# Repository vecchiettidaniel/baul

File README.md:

# caja-negra
Aca va todo lo que quiero tener dispnible, es un pendrive online

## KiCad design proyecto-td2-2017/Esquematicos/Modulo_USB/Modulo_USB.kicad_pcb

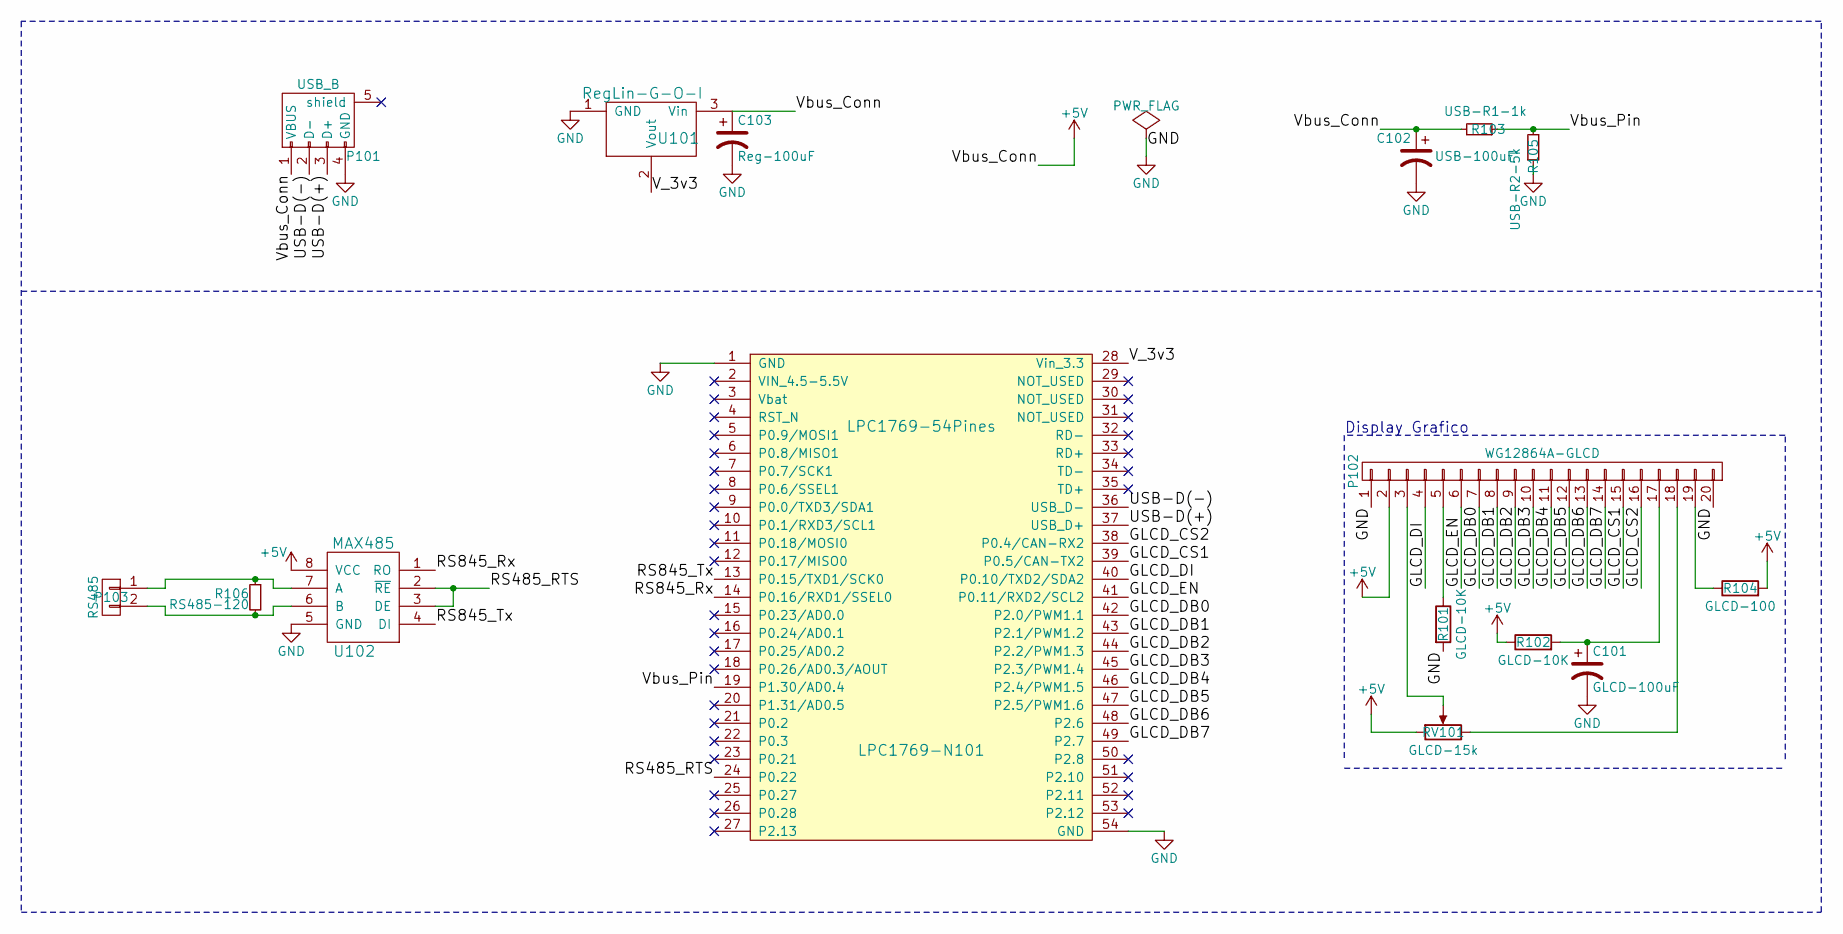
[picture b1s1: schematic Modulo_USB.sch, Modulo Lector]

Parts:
C101: GLCD-100uF; C_Radial_D5_L11_P2
C102: USB-100uF; C_Radial_D5_L11_P2
C103: Reg-100uF; C_Radial_D5_L11_P2
LPC1769-N101: LPC1769-54Pines; LPC1769_Stick-54-pins
P101: USB_B; USB-pads
P102: WG12864A-GLCD; Pin_Header_Straight_1x20
P103: RS485; Pin_Header_Straight_1x02
R101, R102: GLCD-10K; R3
R103: USB-R1-1k; R3
R104: GLCD-100; R3
R105: USB-R2-5k; R3
R106: RS485-120; R3
RV101: GLCD-15k; Potentiometer_Bourns_3296W_3-8Zoll_Inline_ScrewUp
U101: RegLin-G-O-I; TO-220_Neutral123_Vertical
U102: MAX485; DIP-8_W7.62mm_LongPads

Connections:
+5V: C102.1, C103.1, P101.1 (VBUS), P102.2, R102.1, R103.2, R104.2, RV101.1, U101.3 (Vin), U102.8 (VCC)
/GLCD_CS1: LPC1769-N101.39 (P0.5/CAN-TX2), P102.15
/GLCD_CS2: LPC1769-N101.38 (P0.4/CAN-RX2), P102.16
/GLCD_DB0: LPC1769-N101.42 (P2.0/PWM1.1), P102.7
/GLCD_DB1: LPC1769-N101.43 (P2.1/PWM1.2), P102.8
/GLCD_DB2: LPC1769-N101.44 (P2.2/PWM1.3), P102.9
/GLCD_DB3: LPC1769-N101.45 (P2.3/PWM1.4), P102.10
/GLCD_DB4: LPC1769-N101.46 (P2.4/PWM1.5), P102.11
/GLCD_DB5: LPC1769-N101.47 (P2.5/PWM1.6), P102.12
/GLCD_DB6: LPC1769-N101.48 (P2.6), P102.13
/GLCD_DB7: LPC1769-N101.49 (P2.7), P102.14
/GLCD_DI: LPC1769-N101.40 (P0.10/TXD2/SDA2), P102.4
/GLCD_EN: LPC1769-N101.41 (P0.11/RXD2/SCL2), P102.6
/RS485_RTS: LPC1769-N101.24 (P0.22), U102.2 (~RE~), U102.3 (DE)
/RS845_Rx: LPC1769-N101.14 (P0.16/RXD1/SSEL0), U102.1 (RO)
/RS845_Tx: LPC1769-N101.13 (P0.15/TXD1/SCK0), U102.4 (DI)
/USB-D(+): LPC1769-N101.37 (USB_D+), P101.3 (D+)
/USB-D(-): LPC1769-N101.36 (USB_D-), P101.2 (D-)
/V_3v3: LPC1769-N101.28 (Vin_3.3), U101.2 (Vout)
/Vbus_Pin: LPC1769-N101.19 (P1.30/AD0.4), R103.1, R105.2
GND: C101.2, C102.2, C103.2, LPC1769-N101.1 (GND), LPC1769-N101.54 (GND), P101.4 (GND), P102.1, P102.20, R101.2, R105.1, U101.1 (GND), U102.5 (GND)
unnamed: C101.1, P102.17, R102.2
unnamed: P102.3, RV101.2
unnamed: P102.5, R101.1
unnamed: P102.18, RV101.3
unnamed: P102.19, R104.1
unnamed: P103.1, R106.1, U102.7 (A)
unnamed: P103.2, R106.2, U102.6 (B)

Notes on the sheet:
Display Grafico

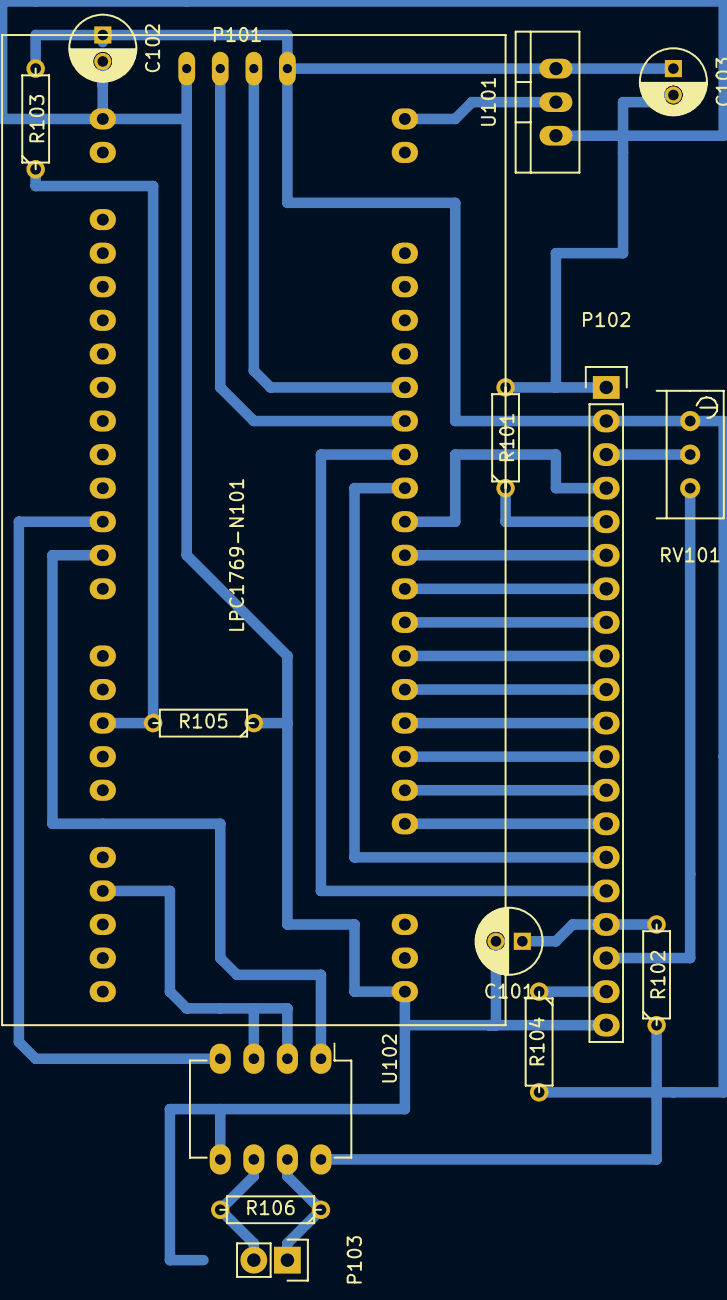
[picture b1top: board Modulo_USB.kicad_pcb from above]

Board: 2 copper layers, 16 parts (0 on the bottom side), 28 nets.

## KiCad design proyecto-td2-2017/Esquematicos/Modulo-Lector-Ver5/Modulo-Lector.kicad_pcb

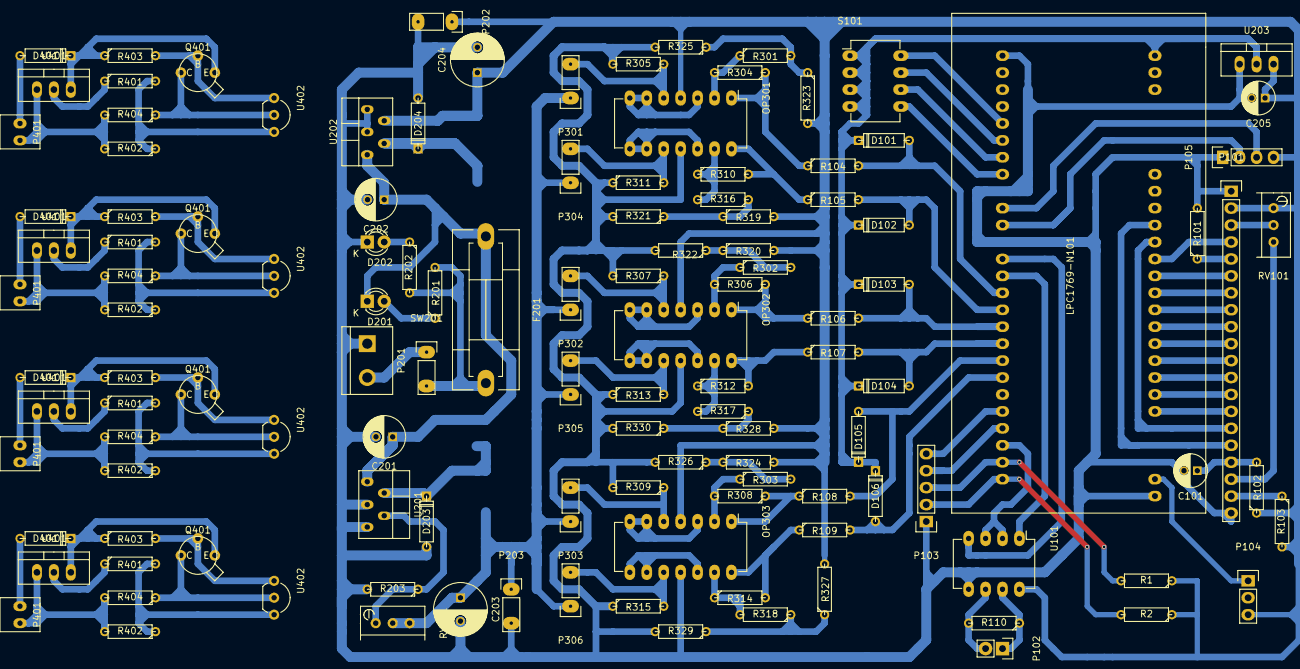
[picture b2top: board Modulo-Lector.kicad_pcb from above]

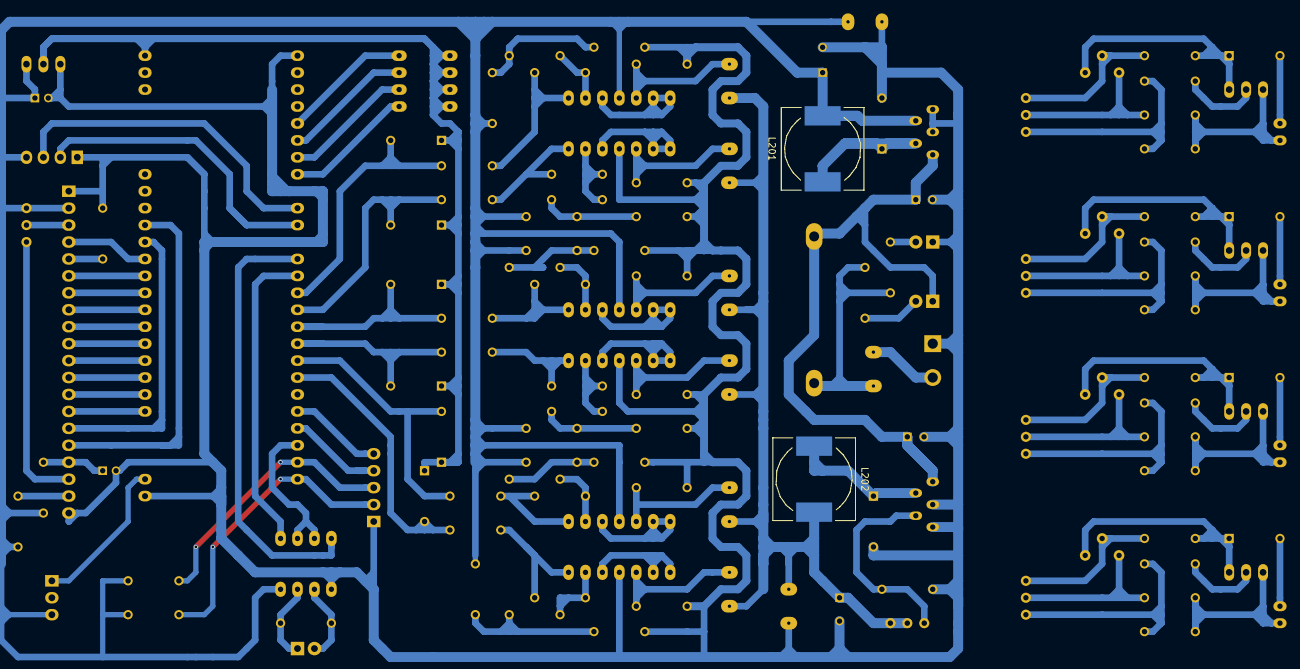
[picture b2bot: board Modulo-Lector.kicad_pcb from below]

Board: 2 copper layers, 126 parts (2 on the bottom side), 88 nets.

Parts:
C101: GLCD-100uF; C_Radial_D5_L11_P2
C201: ADJ_100uF(25v); C_Radial_D6.3_L11.2_P2.5
C202: 5v_100uF(25v); C_Radial_D6.3_L11.2_P2.5
C203: ADJ_330uF(25v); C_Radial_D8_L11.5_P3.5
C204: 5v_330uF; C_Radial_D8_L13_P3.8
C205: 3v3_100uF; C_Radial_D5_L11_P2
D101: Dp-1N5817-L1; D3
D102: Dp-1N5817-L2; D3
D103: Dp-1N5817-L3; D3
D104: Dp-1N5817-L4; D3
D105: Dp-1N5817-L5; D3
D106: Dp-1N5817-L6; D3
D201: LED_FUSE; LED-3MM
D202: PWR_ON_LED; LED-3MM
D203: ADJ_1N5819; D3
D204: 5v_1N5819; D3
D401, D401#2, D401#3, D401#4: 1N4007; D3
F201: Fuse; Fuseholder5x20_horiz_SemiClosed_Casing10x25mm
L201: 5v_330uH; Neosid_Inductor_SM-NE127
L202: ADJ_330uH; Neosid_Inductor_SM-NE127
LPC1769-N101: LPC1769-54Pines; LPC1769_Stick-54-pins
OP301: LM324-A; DIP-14_W7.62mm_LongPads
OP302: LM324-B; DIP-14_W7.62mm_LongPads
OP303: LM324-C; DIP-14_W7.62mm_LongPads
P101: WG12864A-GLCD; Pin_Header_Straight_1x20
P102: RS485; Pin_Header_Straight_1x02
P103: Teclado; Pin_Header_Straight_1x05
P104: CONN_01X03; Pin_Header_Straight_1x03
P105: CONN_01X04; Pin_Header_Straight_1x04
P201: POWER_IN_7-40[v]; bornier2
P202: POWER_Out-(+5V); Pin_1x2_Paso
P203: PWR_Out-Reg; Pin_1x2_Paso
P301: L1-IN; Pin_1x2_Paso
P302: L3-IN; Pin_1x2_Paso
P303: L5-IN; Pin_1x2_Paso
P304: L2-IN; Pin_1x2_Paso
P305: L4-IN; Pin_1x2_Paso
P306: L6-IN; Pin_1x2_Paso
P401, P401#2, P401#3, P401#4: Loop_IN; Pin-1x2
Q401, Q401#2, Q401#3, Q401#4: 2N2907; TBJ-To18
R1: P0.27_Pull_Up; R3
R2: P0.28_Pull_Up; R3
R101, R102: GLCD-10K; R3
R103: GLCD-100; R3
R104: Rp-1k-L1; R3
R105: Rp-1k-L2; R3
R106: Rp-1k-L3; R3
R107: Rp-1k-L4; R3
R108: Rp-1k-L5; R3
R109: Rp-1k-L6; R3
R110: RS485-120; R3
R201: PWR_Fuse_R; R3
R202: PWR_ON_R; R3
R203: ADJ-R1(1k); R3
R301: L1-RG1-2k2; R3
R302: L3-RG1-2k2; R3
R303: L5-RG1-2k2; R3
R304: L1-RG2-1k2; R3
R305: L1-Rin-120; R3
R306: L3-RG2-1k2; R3
R307: L3-Rin-120; R3
R308: L5-RG2-1k2; R3
R309: L5-Rin-120; R3
R310: L2-RG2-1k2; R3
R311: L2-Rin-120; R3
R312: L4-RG2-1k2; R3
R313: L4-Rin-120; R3
R314: L6-RG2-1k2; R3
R315: L6-Rin-120; R3
R316: L2-RG1-2k2; R3
R317: L4-RG1-2k2; R3
R318: L6-RG1-2k2; R3
R319: L2-Ra1-4k7; R3
R320: L3-Ra1-4k7; R3
R321: L2-Ra2-1k; R3
R322: L3-Ra2-1k; R3
R323: L1-Ra1-4k7; R3
R324: L5-Ra1-4k7; R3
R325: L1-Ra2-1k; R3
R326: L5-Ra2-1k; R3
R327: L6-Ra1-4k7; R3
R328: L4-Ra1-4k7; R3
R329: L6-Ra2-1k; R3
R330: L4-Ra2-1k; R3
R401, R401#2, R401#3, R401#4: 330; R3
R402, R402#2, R402#3, R402#4: 120; R3
R403, R403#2, R403#3, R403#4: 4.7k; R3
R404, R404#2, R404#3, R404#4: 36; R3
RV101: GLCD-15k; Potentiometer_Bourns_3296W_3-8Zoll_Inline_ScrewUp
RV201: ADJ_POT; Potentiometer_Bourns_3296W_3-8Zoll_Inline_ScrewUp
S101: SW_DIP_x4; DIP-8_W7.62mm_LongPads
SW201: Power ON/OFF; Pin_1x2_Paso
U101: MAX485; DIP-8_W7.62mm_LongPads
U201: LM2575-ADJ; TO-220-x5-(3_2)
U202: LM2575-5; TO-220-x5-(2_3)
U203: RegLin-G-O-I; TO-220_Neutral123_Vertical
U401, U401#2, U401#3, U401#4: LM317T; TO-220_Neutral123_Vertical
U402, U402#2, U402#3, U402#4: LM35; TO-92_Inline_Wide

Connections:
+5V: C204.1, C205.1, L201.2, OP301.4, OP302.4, OP303.4, P101.2, P104.3, P105.4, P202.1, R1.1, R2.1, R102.1, R103.2, R319.2, R320.2, R323.2, R324.2, R327.2, R328.2, RV101.1, U101.8, U202.4, U203.3
/AD0-Canal-0: D101.2, LPC1769-N101.15, R104.2
/AD0-Canal-1: D102.2, LPC1769-N101.16, R105.2
/AD0-Canal-2: D103.2, LPC1769-N101.17, R106.2
/AD0-Canal-3: D104.2, LPC1769-N101.18, R107.2
/AD0-Canal-4: D105.2, LPC1769-N101.19, R108.2
/AD0-Canal-5: D106.2, LPC1769-N101.20, R109.2
/Dip_SW_01: LPC1769-N101.5, S101.8
/Dip_SW_02: LPC1769-N101.6, S101.7
/Dip_SW_03: LPC1769-N101.7, S101.6
/Dip_SW_04: LPC1769-N101.8, S101.5
/Fuente Alimentación/VIN_7/40V: C201.1, C202.1, D201.1, F201.1, U201.1, U202.1
/GLCD_CS1: LPC1769-N101.39, P101.15
/GLCD_CS2: LPC1769-N101.38, P101.16
/GLCD_DB0: LPC1769-N101.42, P101.7
/GLCD_DB1: LPC1769-N101.43, P101.8
/GLCD_DB2: LPC1769-N101.44, P101.9
/GLCD_DB3: LPC1769-N101.45, P101.10
/GLCD_DB4: LPC1769-N101.46, P101.11
/GLCD_DB5: LPC1769-N101.47, P101.12
/GLCD_DB6: LPC1769-N101.48, P101.13
/GLCD_DB7: LPC1769-N101.49, P101.14
/GLCD_DI: LPC1769-N101.40, P101.4
/GLCD_EN: LPC1769-N101.41, P101.6
/Pin_Extra1: LPC1769-N101.11, P105.2
/Pin_Extra2: LPC1769-N101.10, P105.3
/RS485_RTS: LPC1769-N101.24, U101.2, U101.3
/RS845_Rx: LPC1769-N101.14, U101.1
/RS845_Tx: LPC1769-N101.13, U101.4
/Rele_Cntr: LPC1769-N101.53, P104.1
/Sensores_LM35/LM35-out: Q401.2, Q401#2.2, Q401#3.2, Q401#4.2, R404.1, R404#2.1, R404#3.1, R404#4.1, U402.2, U402#2.2, U402#3.2, U402#4.2
/Sensores_LM35/Loop_V+: D401.1, D401#2.1, D401#3.1, D401#4.1, Q401.3, Q401#2.3, Q401#3.3, Q401#4.3, R403.1, R403#2.1, R403#3.1, R403#4.1, U401.3, U401#2.3, U401#3.3, U401#4.3
/Sensores_LM35/Loop_V-: P401.1, P401#2.1, P401#3.1, P401#4.1, R402.2, R402#2.2, R402#3.2, R402#4.2, R404.2, R404#2.2, R404#3.2, R404#4.2, U401.1, U401#2.1, U401#3.1, U401#4.1
/Tecla_01: LPC1769-N101.22, P103.5
/Tecla_02: LPC1769-N101.23, P103.4
/Tecla_03: LPC1769-N101.25, P103.3, R1.2
/Tecla_04: LPC1769-N101.26, P103.2, R2.2
/Transductores lazo de corriente/Loop-Out-1: OP301.1, R104.1, R304.1
/Transductores lazo de corriente/Loop-Out-2: OP301.14, R105.1, R310.2
/Transductores lazo de corriente/Loop-Out-3: OP302.1, R106.1, R306.1
/Transductores lazo de corriente/Loop-Out-4: OP302.14, R107.1, R312.2
/Transductores lazo de corriente/Loop-Out-5: OP303.1, R108.1, R308.1
/Transductores lazo de corriente/Loop-Out-6: OP303.14, R109.1, R314.2
/Transductores lazo de corriente/Voff_L1: R301.2, R323.1, R325.1
/Transductores lazo de corriente/Voff_L2: R316.1, R319.1, R321.1
/Transductores lazo de corriente/Voff_L3: R302.2, R320.1, R322.1
/Transductores lazo de corriente/Voff_L4: R317.1, R328.1, R330.1
/Transductores lazo de corriente/Voff_L5: R303.2, R324.1, R326.1
/Transductores lazo de corriente/Voff_L6: R318.1, R327.1, R329.1
/VDD_Reg: C203.1, L202.2, P203.1, P301.1, P302.1, P303.1, P304.1, P305.1, P306.1, RV201.2, RV201.3
/V_3v3: D101.1, D102.1, D103.1, D104.1, D105.1, D106.1, LPC1769-N101.28, S101.1, S101.2, S101.3, S101.4, U203.2
GND: C101.2, C201.2, C202.2, C203.2, C204.2, C205.2, D202.1, D203.2, D204.2, LPC1769-N101.1, LPC1769-N101.54, OP301.11, OP302.11, OP303.11, P101.1, P101.20, P103.1, P105.1, P201.1, P202.2, P203.2, R101.2, R203.2, R305.2, R307.2, R309.2, R311.1, R313.1, R315.1, R321.2, R322.2, R325.2, R326.2, R329.2, R330.2, U101.5, U201.3, U201.5, U202.3, U202.5, U203.1
unnamed: C101.1, P101.17, R102.2
unnamed: D201.2, R201.1
unnamed: D202.2, R202.1
unnamed: D203.1, L202.1, U201.2
unnamed: D204.1, L201.1, U202.2
unnamed: D401.2, D401#2.2, D401#3.2, D401#4.2, P401.2, P401#2.2, P401#3.2, P401#4.2
unnamed: F201.2, R201.2, R202.2, SW201.2
unnamed: OP301.2, R301.1, R304.2
unnamed: OP301.3, OP301.6, OP301.7
unnamed: OP301.5, P301.2, R305.1
unnamed: OP301.10, P304.2, R311.2
unnamed: OP301.8, OP301.9, OP301.12
unnamed: OP301.13, R310.1, R316.2
unnamed: OP302.2, R302.1, R306.2
unnamed: OP302.3, OP302.6, OP302.7
unnamed: OP302.5, P302.2, R307.1
unnamed: OP302.10, P305.2, R313.2
unnamed: OP302.8, OP302.9, OP302.12
unnamed: OP302.13, R312.1, R317.2
unnamed: OP303.2, R303.1, R308.2
unnamed: OP303.3, OP303.6, OP303.7
unnamed: OP303.5, P303.2, R309.1
unnamed: OP303.10, P306.2, R315.2
unnamed: OP303.8, OP303.9, OP303.12
unnamed: OP303.13, R314.1, R318.2
unnamed: P101.3, RV101.2
unnamed: P101.5, R101.1
unnamed: P101.18, RV101.3
unnamed: P101.19, R103.1
unnamed: P102.1, R110.1, U101.7
unnamed: P102.2, R110.2, U101.6
unnamed: P201.2, SW201.1
unnamed: Q401.1, Q401#2.1, Q401#3.1, Q401#4.1, R403.2, R403#2.2, R403#3.2, R403#4.2, U402.1, U402#2.1, U402#3.1, U402#4.1
unnamed: R203.1, RV201.1, U201.4
unnamed: R401.1, R401#2.1, R401#3.1, R401#4.1, U401.2, U401#2.2, U401#3.2, U401#4.2
unnamed: R401.2, R401#2.2, R401#3.2, R401#4.2, R402.1, R402#2.1, R402#3.1, R402#4.1, U402.3, U402#2.3, U402#3.3, U402#4.3

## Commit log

2018-09-28 primer commit proyecto td2
2018-09-28 agregue el ssh
2018-11-27 Por si las moscas subi lo de TD3 en 02_cuat
2018-12-07 Receptor_FM es dats de QUCS para Aplicada3
